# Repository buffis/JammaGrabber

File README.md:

# JammaGrabber
Framegrabber for JAMMA

Status : WIP (2015), not yet working, lots of stuff missing.

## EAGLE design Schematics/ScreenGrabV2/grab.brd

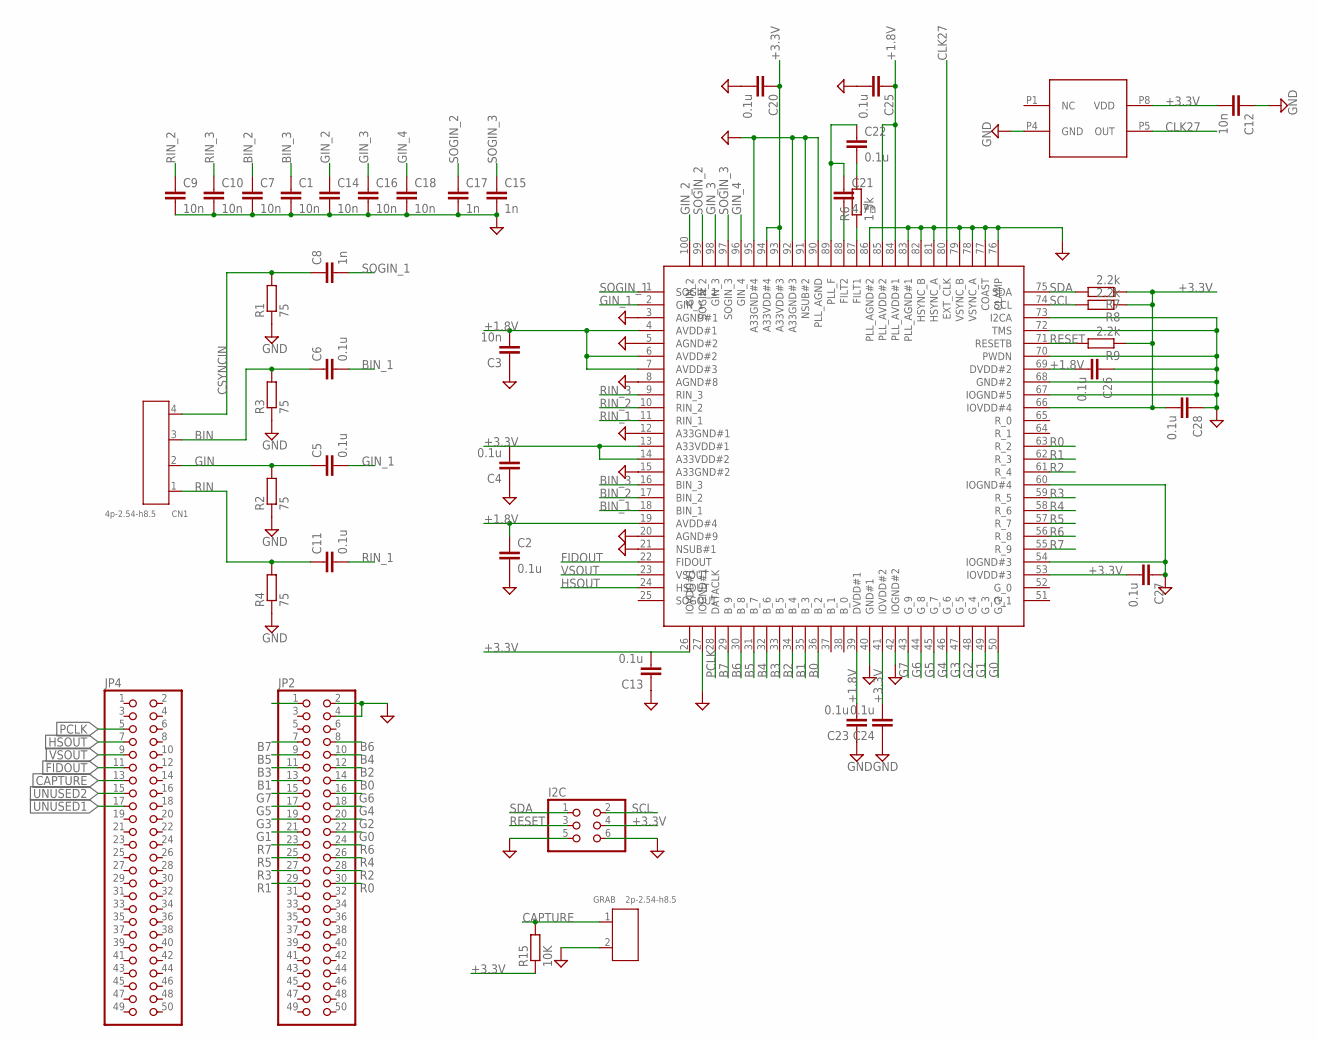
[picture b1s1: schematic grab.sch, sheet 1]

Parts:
27MHZ: ACHL-27MHZ-EK; DIP4
C1, C3, C7, C9, C10, C14, C16, C18: 10n; C0603
C2, C4, C5, C6, C11, C13, C20, C22, C23, C24, C25, C26, C27, C28: 0.1u; C0603
C8, C15, C17: 1n; C0603
C12: 10n; C0805
C21: 4.7n; C0603
CN1: 4p-2.54-h8.5; H4-2.54-8.52X6.3MM
GRAB: 2p-2.54-h8.5; H2-2.54-3.44X6.3MM
I2C: PINHD-2X3; 2X03
JP2, JP4: PINHD-2X25; 2X25
R1, R2, R3, R4: 75; R0603
R6: 1.5k; R0603
R7, R8, R9: 2.2k; R0603
R15: 10K; R0603
TVP7002: TVP7002; TQFP100

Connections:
+1.8V: C2.1, C3.2, C23.2, C25.1, C26.2, TVP7002.4 (AVDD#1), TVP7002.6 (AVDD#2), TVP7002.7 (AVDD#3), TVP7002.19 (AVDD#4), TVP7002.39 (DVDD#1), TVP7002.69 (DVDD#2), TVP7002.84 (PLL_AVDD#1), TVP7002.85 (PLL_AVDD#2); also elsewhere on the board
+3.3V: 27MHZ.P8 (VDD), C4.2, C12.2, C13.2, C20.1, C24.2, C27.2, C28.2, I2C.4, R7.1, R8.1, R9.1, R15.1, TVP7002.13 (A33VDD#1), TVP7002.14 (A33VDD#2), TVP7002.26 (IOVDD#1), TVP7002.41 (IOVDD#2), TVP7002.53 (IOVDD#3), TVP7002.66 (IOVDD#4), TVP7002.93 (A33VDD#3), TVP7002.94 (A33VDD#4); also elsewhere on the board
B0: JP2.14, TVP7002.36 (B_2)
B1: JP2.13, TVP7002.35 (B_3)
B2: JP2.12, TVP7002.34 (B_4)
B3: JP2.11, TVP7002.33 (B_5)
B4: JP2.10, TVP7002.32 (B_6)
B5: JP2.9, TVP7002.31 (B_7)
B6: JP2.8, TVP7002.30 (B_8)
B7: JP2.7, TVP7002.29 (B_9)
BIN: C6.1, CN1.3, R3.2
BIN_1: C6.2, TVP7002.18 (BIN_1)
BIN_2: C7.1, TVP7002.17 (BIN_2)
BIN_3: C1.1, TVP7002.16 (BIN_3)
CAPTURE: GRAB.1, JP4.13, R15.2; also elsewhere on the board
CLK27: 27MHZ.P5 (OUT), TVP7002.80 (EXT_CLK)
CSYNCIN: C8.1, CN1.4, R1.2
FIDOUT: JP4.11, TVP7002.22 (FIDOUT)
G0: JP2.22, TVP7002.50 (G_2)
G1: JP2.21, TVP7002.49 (G_3)
G2: JP2.20, TVP7002.48 (G_4)
G3: JP2.19, TVP7002.47 (G_5)
G4: JP2.18, TVP7002.46 (G_6)
G5: JP2.17, TVP7002.45 (G_7)
G6: JP2.16, TVP7002.44 (G_8)
G7: JP2.15, TVP7002.43 (G_9)
GIN: C5.1, CN1.2, R2.2
GIN_1: C5.2, TVP7002.2 (GIN_1)
GIN_2: C14.1, TVP7002.100 (GIN_2)
GIN_3: C16.1, TVP7002.98 (GIN_3)
GIN_4: C18.1, TVP7002.96 (GIN_4)
GND: 27MHZ.P4 (GND), C1.2, C2.2, C3.1, C4.1, C7.2, C9.2, C10.2, C12.1, C13.1, C14.2, C15.2, C16.2, C17.2, C18.2, C20.2, C23.1, C24.1, C25.2, C26.1, C27.1, C28.1, GRAB.2, I2C.5, I2C.6, JP2.2, JP2.4, R1.1, R2.1, R3.1, R4.1, TVP7002.3 (AGND#1), TVP7002.5 (AGND#2), TVP7002.8 (AGND#8), TVP7002.12 (A33GND#1), TVP7002.15 (A33GND#2), TVP7002.20 (AGND#9), TVP7002.21 (NSUB#1), TVP7002.27 (IOGND#1), TVP7002.40 (GND#1), TVP7002.42 (IOGND#2), TVP7002.54 (IOGND#3), TVP7002.60 (IOGND#4), TVP7002.67 (IOGND#5), TVP7002.68 (GND#2), TVP7002.70 (PWDN), TVP7002.72 (TMS), TVP7002.73 (I2CA), TVP7002.76 (CLAMP), TVP7002.77 (COAST), TVP7002.78 (VSYNC_A), TVP7002.79 (VSYNC_B), TVP7002.81 (HSYNC_A), TVP7002.82 (HSYNC_B), TVP7002.83 (PLL_AGND#1), TVP7002.86 (PLL_AGND#2), TVP7002.90 (PLL_AGND), TVP7002.91 (NSUB#2), TVP7002.92 (A33GND#3), TVP7002.95 (A33GND#4); also elsewhere on the board
HSOUT: JP4.7, TVP7002.24 (HSOUT)
unnamed: C21.2, TVP7002.88 (FILT2)
unnamed: R6.1, TVP7002.87 (FILT1)
unnamed: C22.2, R6.2
unnamed: C21.1, C22.1, TVP7002.89 (PLL_F)
PCLK: JP4.5, TVP7002.28 (DATACLK)
R0: JP2.30, TVP7002.63 (R_2)
R1: JP2.29, TVP7002.62 (R_3)
R2: JP2.28, TVP7002.61 (R_4)
R3: JP2.27, TVP7002.59 (R_5)
R4: JP2.26, TVP7002.58 (R_6)
R5: JP2.25, TVP7002.57 (R_7)
R6: JP2.24, TVP7002.56 (R_8)
R7: JP2.23, TVP7002.55 (R_9)
RESET: I2C.3, R9.2, TVP7002.71 (RESETB); also elsewhere on the board
RIN: C11.1, CN1.1, R4.2
RIN_1: C11.2, TVP7002.11 (RIN_1)
RIN_2: C9.1, TVP7002.10 (RIN_2)
RIN_3: C10.1, TVP7002.9 (RIN_3)
SCL: I2C.2, R8.2, TVP7002.74 (SCL); also elsewhere on the board
SDA: I2C.1, R7.2, TVP7002.75 (SDA); also elsewhere on the board
SOGIN_1: C8.2, TVP7002.1 (SOGIN_1)
SOGIN_2: C17.1, TVP7002.99 (SOGIN_2)
SOGIN_3: C15.1, TVP7002.97 (SOGIN_3)
UNUSED1: JP4.17; also elsewhere on the board
UNUSED2: JP4.15; also elsewhere on the board
VSOUT: JP4.9, TVP7002.23 (VSOUT)

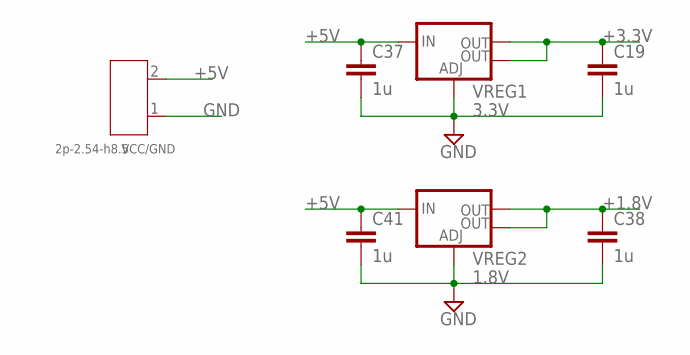
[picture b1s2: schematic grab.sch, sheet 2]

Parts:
C19, C37, C38, C41: 1u; C0603
VCC/GND: 2p-2.54-h8.5; H2-2.54-3.44X6.3MM
VREG1: 3.3V; SOT223
VREG2: 1.8V; SOT223

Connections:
+1.8V: C38.1, VREG2.2 (OUT), VREG2.4 (OUT); also elsewhere on the board
+3.3V: C19.1, VREG1.2 (OUT), VREG1.4 (OUT); also elsewhere on the board
+5V: C37.1, C41.1, VCC/GND.2, VREG1.3 (IN), VREG2.3 (IN); also elsewhere on the board
GND: C19.2, C37.2, C38.2, C41.2, VCC/GND.1, VREG1.1 (ADJ), VREG2.1 (ADJ); also elsewhere on the board

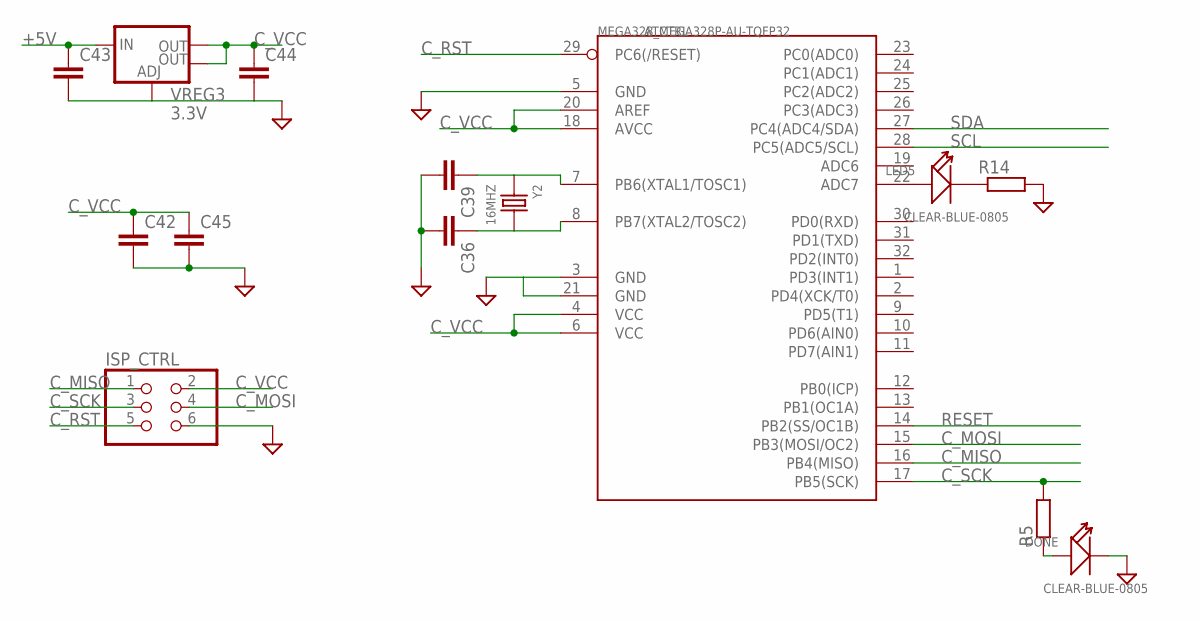
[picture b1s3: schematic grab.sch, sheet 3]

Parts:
C36, C39, C42, C43, C44, C45: C-EUC0603; C0603
DONE: CLEAR-BLUE-0805; LED-0805
ISP_CTRL: PINHD-2X3; 2X03
LED5: CLEAR-BLUE-0805; LED-0805
MEGA328_CTRL: ATMEGA328P-AU-TQFP32; TQFP32-0.8-7X7MM
R5, R14: R-EU_R0603; R0603
VREG3: 3.3V; SOT223
Y2: 16MHZ; X2-SMD-5.0X3.2X1.3MM

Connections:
+5V: C43.1, VREG3.3 (IN); also elsewhere on the board
C_MISO: ISP_CTRL.1, MEGA328_CTRL.16 (PB4(MISO))
C_MOSI: ISP_CTRL.4, MEGA328_CTRL.15 (PB3(MOSI/OC2))
C_RST: ISP_CTRL.5, MEGA328_CTRL.29 (PC6(/RESET))
C_SCK: ISP_CTRL.3, MEGA328_CTRL.17 (PB5(SCK)), R5.2
C_VCC: C42.1, C44.1, C45.1, ISP_CTRL.2, MEGA328_CTRL.4 (VCC), MEGA328_CTRL.6 (VCC), MEGA328_CTRL.18 (AVCC), MEGA328_CTRL.20 (AREF), VREG3.2 (OUT), VREG3.4 (OUT)
GND: C36.2, C39.2, C42.2, C43.2, C44.2, C45.2, DONE.-, ISP_CTRL.6, MEGA328_CTRL.3 (GND), MEGA328_CTRL.5 (GND), MEGA328_CTRL.21 (GND), R14.2, VREG3.1 (ADJ); also elsewhere on the board
unnamed: C39.1, MEGA328_CTRL.7 (PB6(XTAL1/TOSC1)), Y2.1
unnamed: C36.1, MEGA328_CTRL.8 (PB7(XTAL2/TOSC2)), Y2.2
unnamed: DONE.+, R5.1
unnamed: LED5.+, MEGA328_CTRL.22 (ADC7)
unnamed: LED5.-, R14.1
RESET: MEGA328_CTRL.14 (PB2(SS/OC1B)); also elsewhere on the board
SCL: MEGA328_CTRL.28 (PC5(ADC5/SCL)); also elsewhere on the board
SDA: MEGA328_CTRL.27 (PC4(ADC4/SDA)); also elsewhere on the board

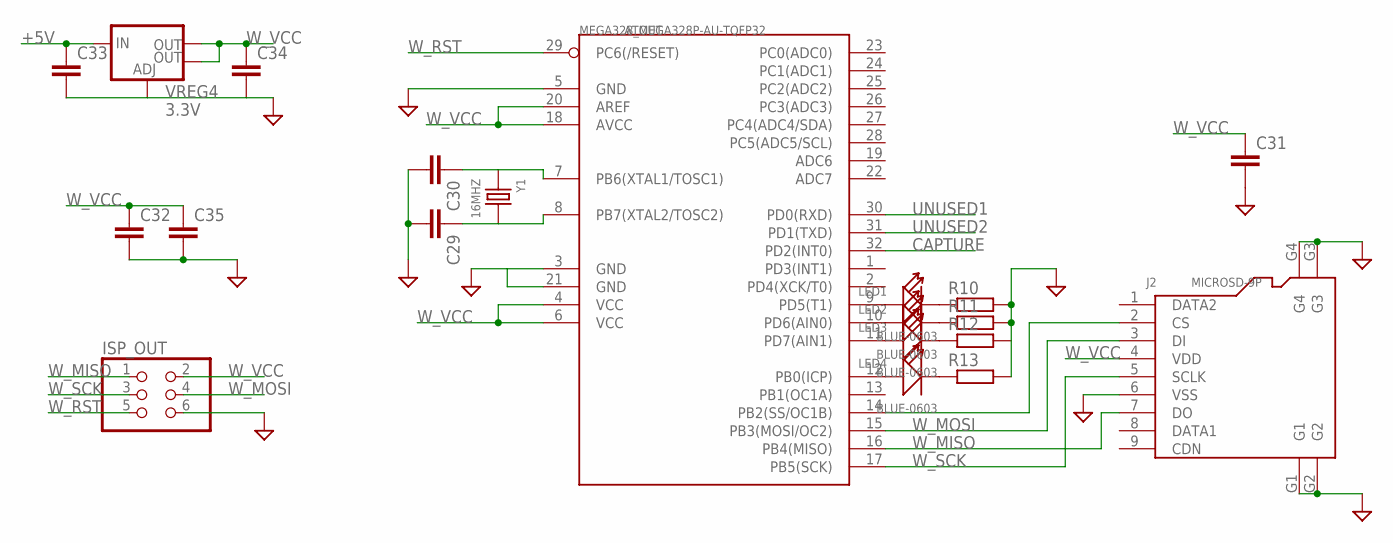
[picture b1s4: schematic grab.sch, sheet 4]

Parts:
C29, C30, C31, C32, C33, C34, C35: C-EUC0603; C0603
ISP_OUT: PINHD-2X3; 2X03
J2: MICROSD-9P; MICRO-SD9+4P-SMD-16.1X14.5X1.85MM
LED1, LED2, LED3, LED4: BLUE-0603; LED-0603
MEGA328_OUT: ATMEGA328P-AU-TQFP32; TQFP32-0.8-7X7MM
R10, R11, R12, R13: R-EU_R0603; R0603
VREG4: 3.3V; SOT223
Y1: 16MHZ; X2-SMD-5.0X3.2X1.3MM

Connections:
+5V: C33.1, VREG4.3 (IN); also elsewhere on the board
CAPTURE: MEGA328_OUT.32 (PD2(INT0)); also elsewhere on the board
GND: C29.2, C30.2, C31.2, C32.2, C33.2, C34.2, C35.2, ISP_OUT.6, J2.6 (VSS), J2.G1, J2.G2, J2.G3, J2.G4, MEGA328_OUT.3 (GND), MEGA328_OUT.5 (GND), MEGA328_OUT.21 (GND), R10.2, R11.2, R13.2, VREG4.1 (ADJ); also elsewhere on the board
unnamed: J2.2 (CS), MEGA328_OUT.14 (PB2(SS/OC1B))
unnamed: LED1.+, MEGA328_OUT.9 (PD5(T1))
unnamed: LED2.+, MEGA328_OUT.10 (PD6(AIN0))
unnamed: LED3.+, MEGA328_OUT.11 (PD7(AIN1))
unnamed: LED4.+, MEGA328_OUT.12 (PB0(ICP))
unnamed: C30.1, MEGA328_OUT.7 (PB6(XTAL1/TOSC1)), Y1.1
unnamed: C29.1, MEGA328_OUT.8 (PB7(XTAL2/TOSC2)), Y1.2
unnamed: LED1.-, R10.1
unnamed: LED2.-, R11.1
unnamed: LED3.-, R12.1
unnamed: LED4.-, R13.1
UNUSED1: MEGA328_OUT.30 (PD0(RXD)); also elsewhere on the board
UNUSED2: MEGA328_OUT.31 (PD1(TXD)); also elsewhere on the board
W_MISO: ISP_OUT.1, J2.7 (DO), MEGA328_OUT.16 (PB4(MISO))
W_MOSI: ISP_OUT.4, J2.3 (DI), MEGA328_OUT.15 (PB3(MOSI/OC2))
W_RST: ISP_OUT.5, MEGA328_OUT.29 (PC6(/RESET))
W_SCK: ISP_OUT.3, J2.5 (SCLK), MEGA328_OUT.17 (PB5(SCK))
W_VCC: C31.1, C32.1, C34.1, C35.1, ISP_OUT.2, J2.4 (VDD), MEGA328_OUT.4 (VCC), MEGA328_OUT.6 (VCC), MEGA328_OUT.18 (AVCC), MEGA328_OUT.20 (AREF), VREG4.2 (OUT), VREG4.4 (OUT)

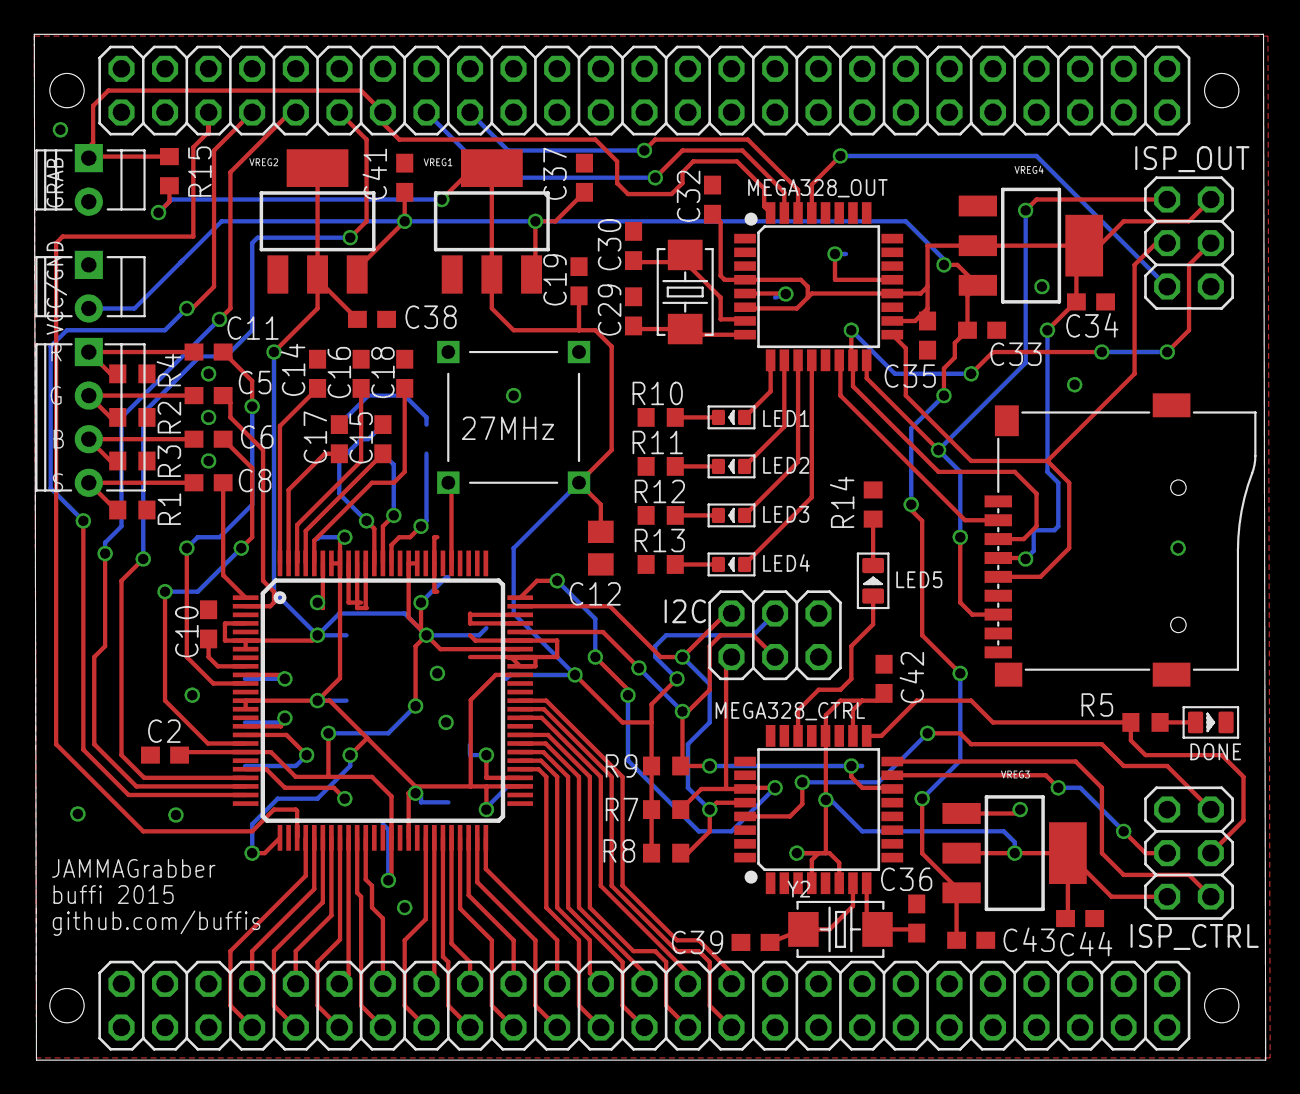
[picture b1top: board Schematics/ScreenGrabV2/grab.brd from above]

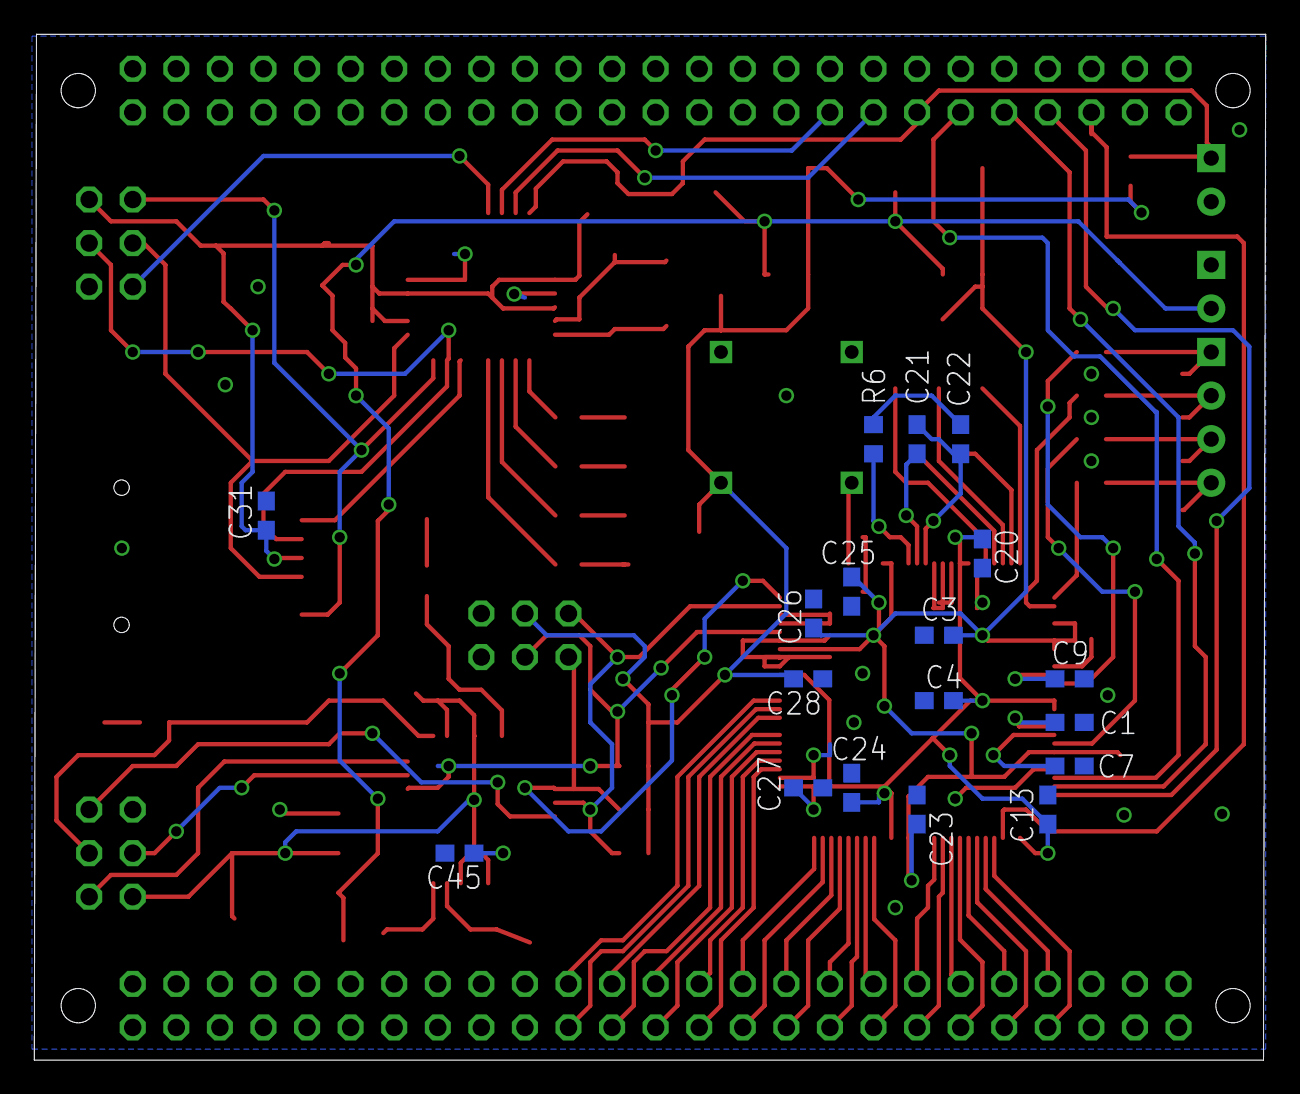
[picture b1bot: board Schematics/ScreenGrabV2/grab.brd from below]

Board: 2 copper layers, 71.8 x 59.8 mm, 84 parts (18 on the bottom side), 86 nets.

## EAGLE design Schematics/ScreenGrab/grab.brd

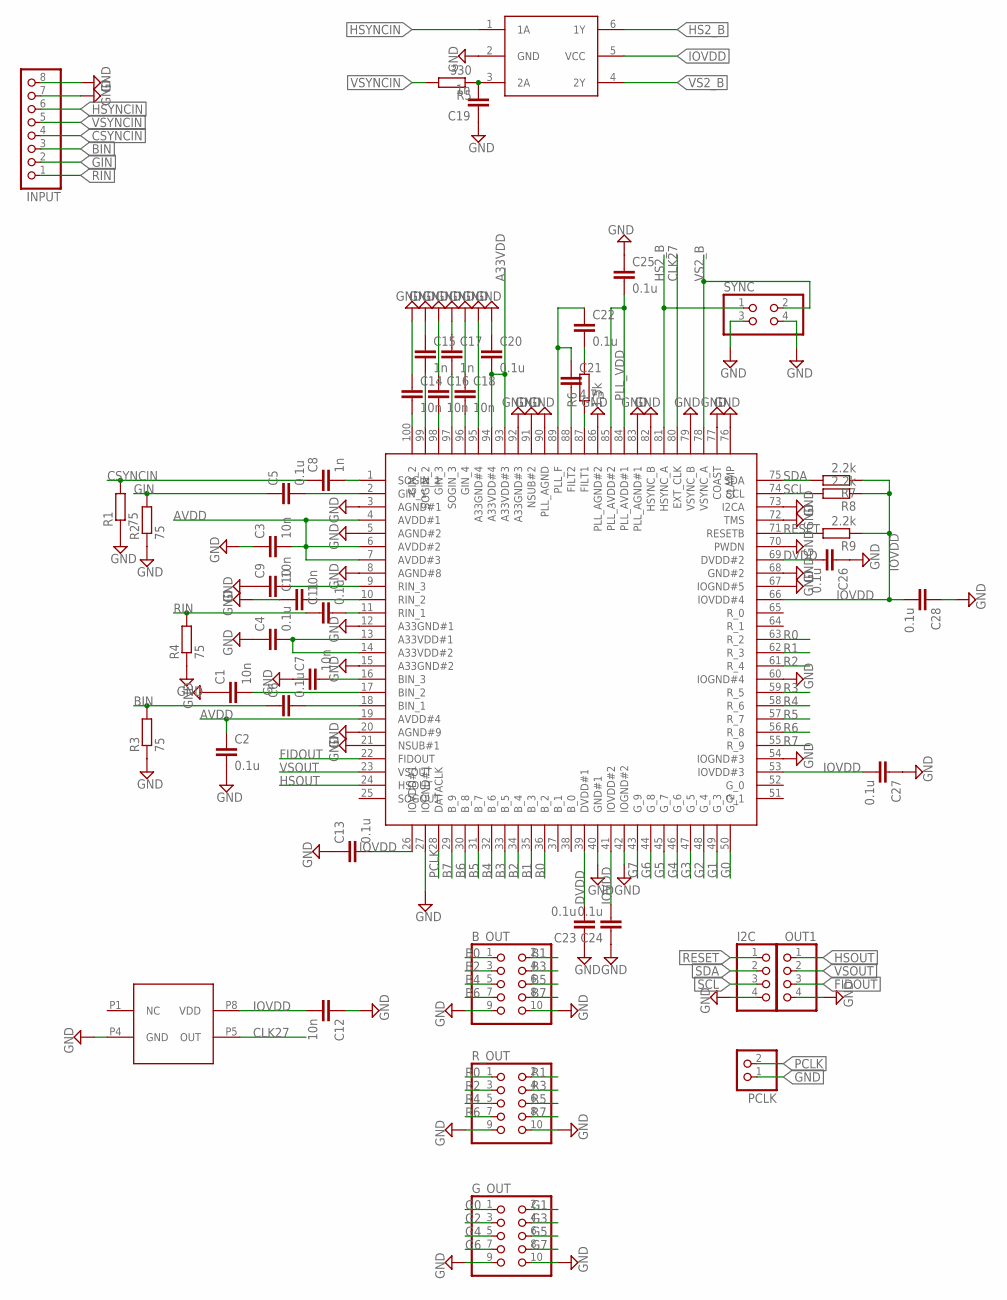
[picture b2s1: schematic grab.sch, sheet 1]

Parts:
27MHZ: ACHL-27MHZ-EK; DIP4
B_OUT: PINHD-2X5; 2X05
C1, C3, C7, C9, C10, C14, C16, C18: 10n; C0603
C2, C4, C5, C6, C11, C13, C20, C22, C23, C24, C25, C26, C27, C28: 0.1u; C0603
C8, C15, C17: 1n; C0603
C12: 10n; C0805
C19: 1n; C0805
C21: 4.7n; C0603
G_OUT: PINHD-2X5; 2X05
I2C: PINHD-1X4; 1X04
INPUT: PINHD-1X8; 1X08
OUT1: PINHD-1X4; 1X04
PCLK: PINHD-1X2; 1X02
R1, R2, R3, R4: 75; R0603
R5: 330; R0805
R6: 1.5k; R0603
R7, R8, R9: 2.2k; R0603
R_OUT: PINHD-2X5; 2X05
SYNC: PINHD-2X2; 2X02
SYNC_IC: SN74LVC2G17SC-70-6; SC70-6L
TVP7002: TVP7002; TQFP100

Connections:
A33VDD: C4.2, C20.2, TVP7002.13 (A33VDD#1), TVP7002.14 (A33VDD#2), TVP7002.93 (A33VDD#3), TVP7002.94 (A33VDD#4); also elsewhere on the board
AVDD: C2.1, C3.2, TVP7002.4 (AVDD#1), TVP7002.6 (AVDD#2), TVP7002.7 (AVDD#3), TVP7002.19 (AVDD#4); also elsewhere on the board
B0: B_OUT.1, TVP7002.36 (B_2)
B1: B_OUT.2, TVP7002.35 (B_3)
B2: B_OUT.3, TVP7002.34 (B_4)
B3: B_OUT.4, TVP7002.33 (B_5)
B4: B_OUT.5, TVP7002.32 (B_6)
B5: B_OUT.6, TVP7002.31 (B_7)
B6: B_OUT.7, TVP7002.30 (B_8)
B7: B_OUT.8, TVP7002.29 (B_9)
BIN: C6.1, INPUT.3, R3.2
CLK27: 27MHZ.P5 (OUT), TVP7002.80 (EXT_CLK)
CSYNCIN: C8.1, INPUT.4, R1.2
DVDD: C23.2, C26.2, TVP7002.39 (DVDD#1), TVP7002.69 (DVDD#2); also elsewhere on the board
FIDOUT: OUT1.3, TVP7002.22 (FIDOUT)
G0: G_OUT.1, TVP7002.50 (G_2)
G1: G_OUT.2, TVP7002.49 (G_3)
G2: G_OUT.3, TVP7002.48 (G_4)
G3: G_OUT.4, TVP7002.47 (G_5)
G4: G_OUT.5, TVP7002.46 (G_6)
G5: G_OUT.6, TVP7002.45 (G_7)
G6: G_OUT.7, TVP7002.44 (G_8)
G7: G_OUT.8, TVP7002.43 (G_9)
GIN: C5.1, INPUT.2, R2.2
GND: 27MHZ.P4 (GND), B_OUT.9, B_OUT.10, C1.1, C2.2, C3.1, C4.1, C7.1, C9.1, C10.1, C12.1, C13.1, C14.1, C15.1, C16.1, C17.1, C18.1, C19.1, C20.1, C23.1, C24.1, C25.1, C26.1, C27.1, C28.1, G_OUT.9, G_OUT.10, I2C.4, INPUT.7, INPUT.8, OUT1.4, PCLK.1, R1.1, R2.1, R3.1, R4.1, R_OUT.9, R_OUT.10, SYNC.3, SYNC.4, SYNC_IC.2 (GND), TVP7002.3 (AGND#1), TVP7002.5 (AGND#2), TVP7002.8 (AGND#8), TVP7002.12 (A33GND#1), TVP7002.15 (A33GND#2), TVP7002.20 (AGND#9), TVP7002.21 (NSUB#1), TVP7002.27 (IOGND#1), TVP7002.40 (GND#1), TVP7002.42 (IOGND#2), TVP7002.54 (IOGND#3), TVP7002.60 (IOGND#4), TVP7002.67 (IOGND#5), TVP7002.68 (GND#2), TVP7002.70 (PWDN), TVP7002.72 (TMS), TVP7002.73 (I2CA), TVP7002.76 (CLAMP), TVP7002.77 (COAST), TVP7002.79 (VSYNC_B), TVP7002.82 (HSYNC_B), TVP7002.83 (PLL_AGND#1), TVP7002.86 (PLL_AGND#2), TVP7002.90 (PLL_AGND), TVP7002.91 (NSUB#2), TVP7002.92 (A33GND#3), TVP7002.95 (A33GND#4); also elsewhere on the board
HS2_B: SYNC.1, SYNC_IC.6 (1Y), TVP7002.81 (HSYNC_A)
HSOUT: OUT1.1, TVP7002.24 (HSOUT)
HSYNCIN: INPUT.6, SYNC_IC.1 (1A)
IOVDD: 27MHZ.P8 (VDD), C12.2, C13.2, C24.2, C27.2, C28.2, R7.1, R8.1, R9.1, SYNC_IC.5 (VCC), TVP7002.26 (IOVDD#1), TVP7002.41 (IOVDD#2), TVP7002.53 (IOVDD#3), TVP7002.66 (IOVDD#4); also elsewhere on the board
unnamed: C8.2, TVP7002.1 (SOGIN_1)
unnamed: C5.2, TVP7002.2 (GIN_1)
unnamed: C11.2, TVP7002.11 (RIN_1)
unnamed: C19.2, R5.1, SYNC_IC.3 (2A)
unnamed: C7.2, TVP7002.16 (BIN_3)
unnamed: C14.2, TVP7002.100 (GIN_2)
unnamed: C15.2, TVP7002.99 (SOGIN_2)
unnamed: C16.2, TVP7002.98 (GIN_3)
unnamed: C9.2, TVP7002.9 (RIN_3)
unnamed: C10.2, TVP7002.10 (RIN_2)
unnamed: C1.2, TVP7002.17 (BIN_2)
unnamed: C6.2, TVP7002.18 (BIN_1)
unnamed: C17.2, TVP7002.97 (SOGIN_3)
unnamed: C18.2, TVP7002.96 (GIN_4)
unnamed: C21.2, TVP7002.88 (FILT2)
unnamed: R6.1, TVP7002.87 (FILT1)
unnamed: C22.2, R6.2
unnamed: C21.1, C22.1, TVP7002.89 (PLL_F)
PCLK: PCLK.2, TVP7002.28 (DATACLK)
PLL_VDD: C25.2, TVP7002.84 (PLL_AVDD#1), TVP7002.85 (PLL_AVDD#2); also elsewhere on the board
R0: R_OUT.1, TVP7002.63 (R_2)
R1: R_OUT.2, TVP7002.62 (R_3)
R2: R_OUT.3, TVP7002.61 (R_4)
R3: R_OUT.4, TVP7002.59 (R_5)
R4: R_OUT.5, TVP7002.58 (R_6)
R5: R_OUT.6, TVP7002.57 (R_7)
R6: R_OUT.7, TVP7002.56 (R_8)
R7: R_OUT.8, TVP7002.55 (R_9)
RESET: I2C.1, R9.2, TVP7002.71 (RESETB)
RIN: C11.1, INPUT.1, R4.2
SCL: I2C.3, R8.2, TVP7002.74 (SCL)
SDA: I2C.2, R7.2, TVP7002.75 (SDA)
VS2_B: SYNC.2, SYNC_IC.4 (2Y), TVP7002.78 (VSYNC_A)
VSOUT: OUT1.2, TVP7002.23 (VSOUT)
VSYNCIN: INPUT.5, R5.2

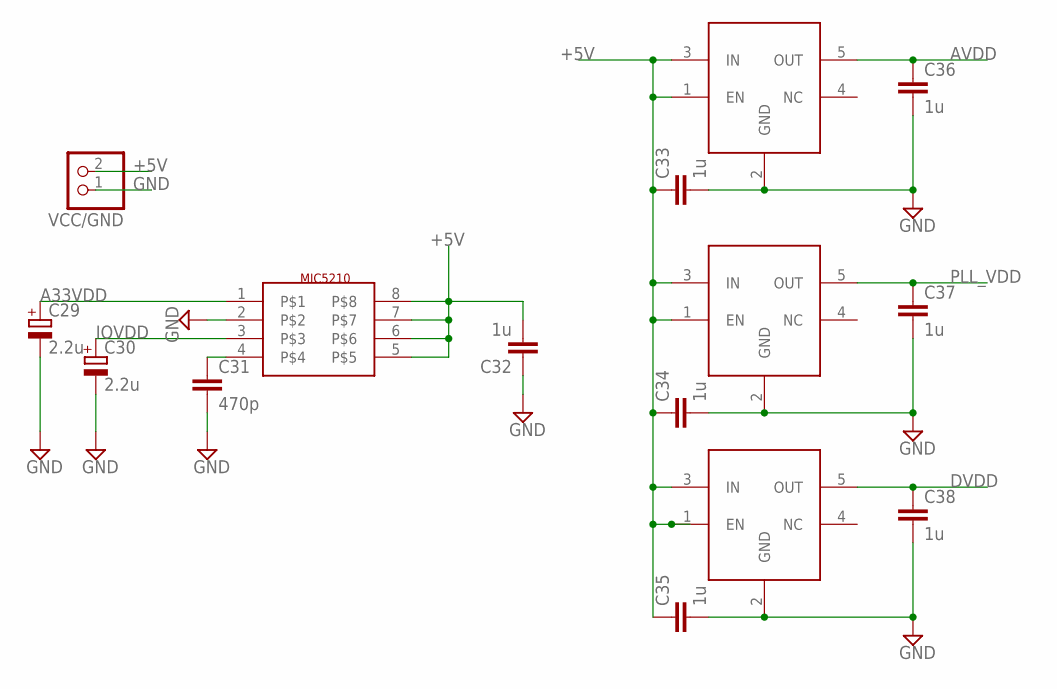
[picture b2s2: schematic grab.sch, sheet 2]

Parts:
C29, C30: 2.2u; B45181A
C31: 470p; C0805
C32, C33, C34, C35, C36, C37, C38: 1u; C0805
VCC/GND: PINHD-1X2; 1X02
VREG1: MIC5210MSOP8; MSOP8
VREG2, VREG3, VREG4: TLV70019SOT23-5L; SOT23-5L

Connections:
+5V: C32.2, C33.1, C34.1, C35.1, VCC/GND.2, VREG1.5, VREG1.6, VREG1.7, VREG1.8, VREG2.1 (EN), VREG2.3 (IN), VREG3.1 (EN), VREG3.3 (IN), VREG4.1 (EN), VREG4.3 (IN)
A33VDD: C29.+, VREG1.1; also elsewhere on the board
AVDD: C36.1, VREG2.5 (OUT); also elsewhere on the board
DVDD: C38.1, VREG4.5 (OUT); also elsewhere on the board
GND: C29.-, C30.-, C31.2, C32.1, C33.2, C34.2, C35.2, C36.2, C37.2, C38.2, VCC/GND.1, VREG1.2, VREG2.2 (GND), VREG3.2 (GND), VREG4.2 (GND); also elsewhere on the board
IOVDD: C30.+, VREG1.3; also elsewhere on the board
unnamed: C31.1, VREG1.4
PLL_VDD: C37.1, VREG3.5 (OUT); also elsewhere on the board

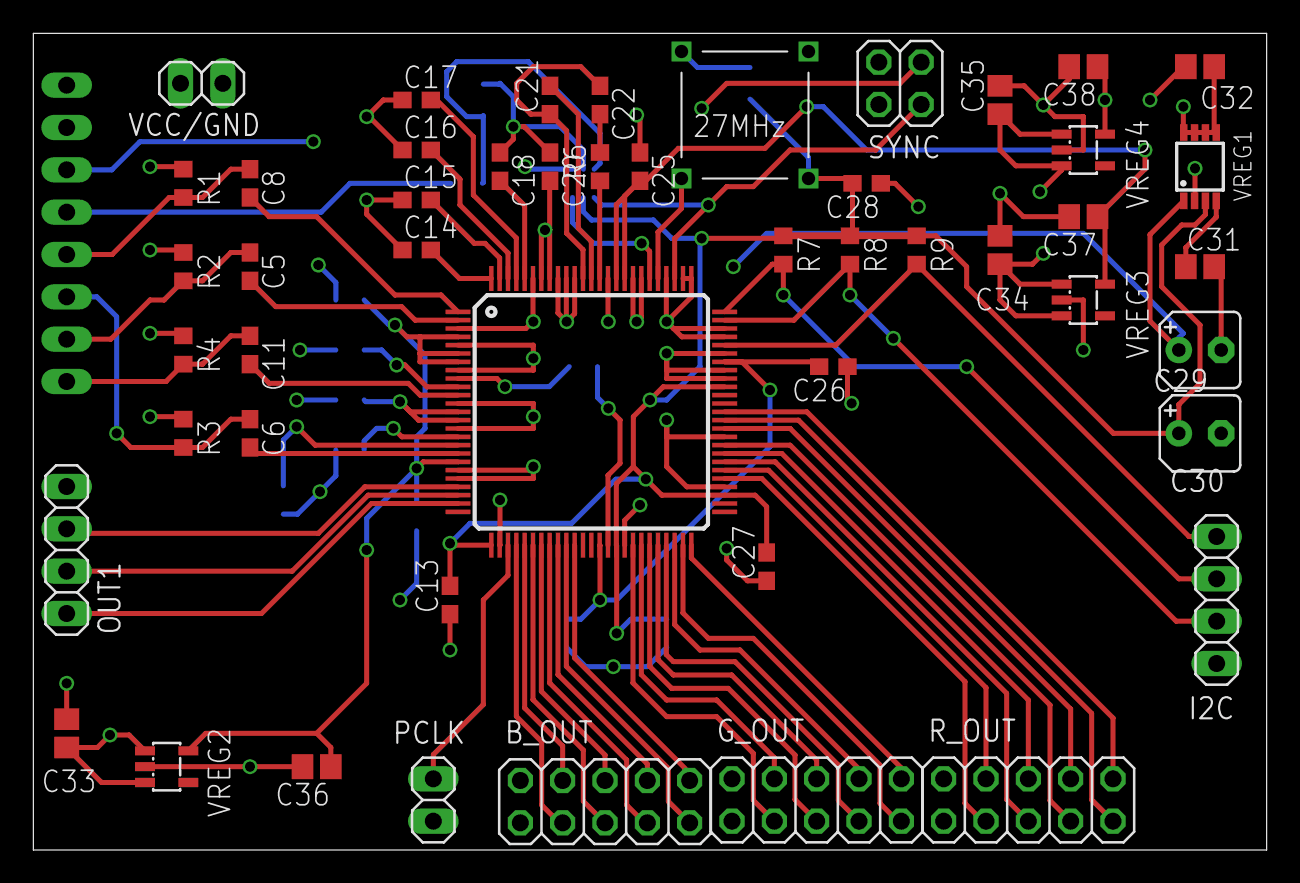
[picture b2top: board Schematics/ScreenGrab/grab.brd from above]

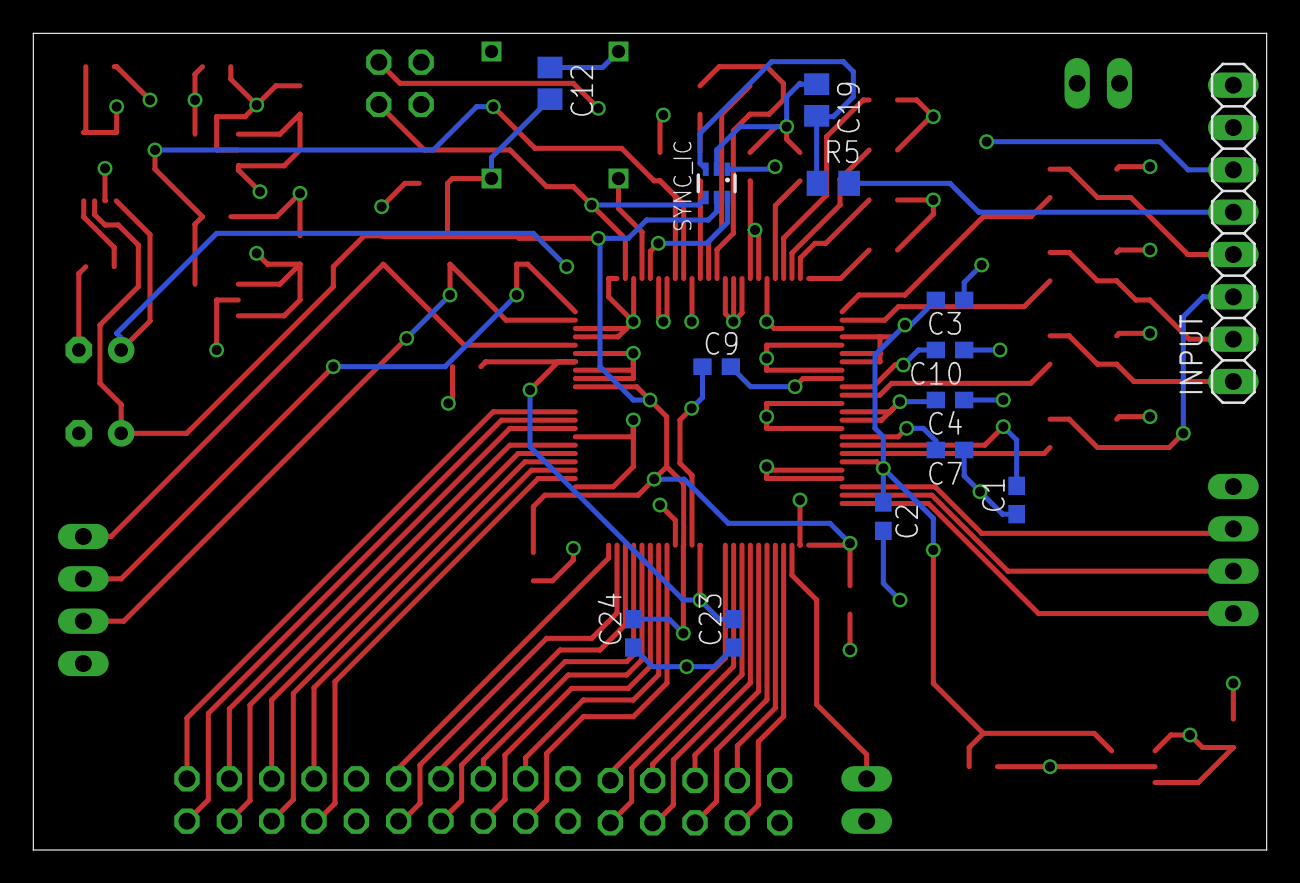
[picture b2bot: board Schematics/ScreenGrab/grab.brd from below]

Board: 4 copper layers, 74.0 x 49.0 mm, 63 parts (14 on the bottom side), 66 nets.

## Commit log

2015-08-28 Initial commit. moving stuff into this repo
2015-08-29 Added schematics
2015-08-29 Schematic routed
2015-08-30 Schematic update
2015-08-30 Made the SD write work

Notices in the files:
parts and their libraries:
SparkFun-PowerIC: Licensing: Creative Commons ShareAlike 4.0 International - https://creativecommons.org/licenses/by-sa/4.0
